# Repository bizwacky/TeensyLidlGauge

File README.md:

# Teensy Lidl Gauge

This is a set of gauges for my BMW E30 rally car, designed to be viewed in the peripheral vision, alerting to situations that need attention or immediate action and otherwise mostly being ignored while my OODA loop focuses on the stage ahead.

Three ER-TFT2.79-1 bar displays (NV3007 controller), driven over SPI by a
SparkFun MicroMod Teensy ,
fed by CAN data from the rusEFI ECU (a Super uaEFI), the JK BMS and the
car's two planned dingoFW PDMs. The gauge also reads the roof switch panel (six
switches, five pots) and sends it to the PDMs over CAN - it is the car's
light-switch node - and drives three PWM speed signals for the cabin fans.

This repository holds the firmware (`src/`, `lib/`, `docs/`) and, in
[`hardware/`](hardware/), the KiCad project, fab outputs and the 3D-printed
enclosure. The full hardware/software plan (`Rally CAN Gauge Project Plan`)
lives outside this repository.

**Status (Nov 2026):** the v1.0 board is at the ordering stage.

## Design philosophy

- Most of the time the right amount of attention to pay the gauge is none. 
-  Red: The car is about to blow up.
  Yellow: Start worrying, keep an eye on it. Blue: information. A one-line
  banner names the problem (`OIL LOW`, `PUMP FLT`), critical banners flash
  at 1 Hz, and  have GPWS-style voice callouts
- Input code establishes what is (temperatures, pressures, link freshness); one alarm table decides what
  matters; the screens, LEDs and audio only render its verdicts. No
  display code ever touches a threshold. 
- A dead sensor or a dropped CAN link draws as
  `--`. Stale data raises no alarms of its own.
- The rotary dial is the only control: bright,
- medium, dark (night colours turn every blue element amber, which is kinder
  to dark-adapted eyes), debug, silent, fuel fill and displays off. One more
  detent, well away from those, is a car-park light show.
- All vehicle I/O comes through one sealed 26-pin Superseal. The 12 V front end has reverse-polarity protection, a
  36 V TVS, a switching 5 V module and a separate 3.3 V LDO. The fuel
  record (in CRC'd rotating slots) and a black-box log live in F-RAM, a hardware watchdog resets hung
  firmware within a second. 

## Hardware

100 x 100 mm, four layers (Signal / GND / GND / Signal), 1.6 mm, laid out in
KiCad 10 against JLCPCB's rules and their JLC04161H-7628 stackup. The J2 pin-out is printed on the back of the board.

| Block | Parts |
|---|---|
| Processor | SparkFun MicroMod Teensy in a TE 2199230-4 M.2 (E-key) socket |
| Displays | 3x ER-TFT2.79-1 on 10-pin 0.5 mm FPC connectors (Amphenol SFV10R-2STE1HLF), one SPI bus each; PWM backlights through three low-side N-FETs |
| Vehicle connector | TE Superseal 1.0, 26-pin (6473711-1): +12 V, CAN, six switch inputs, five pots, fuel sender, rotary dial, speaker, LED-strip data and 5 V, three fan PWM outputs |
| CAN | TI TCAN1051HGV-Q1 |
| Power | Traco TSR 3-2450N (5 V, 3 A), TI TLV75733P (3.3 V LDO), Panjit PJQ4465AP reverse-polarity P-FET, SMCJ36CA TVS |
| Logging and sensors | 1 Mbit I2C F-RAM (FM24VN10 / FM24V10), ST LSM6DSV320X IMU (±320 g), CR2450 cell for the clock |
| Audio | DFRobot DFPlayer Mini (DFR0299)|
| USB | 6-pin JST-PH (J1) to an Adafruit 6153 panel-mount USB-C, TPD2E2U06 ESD protection |

### What is in `hardware/`

| Path | What |
|---|---|
| `TeensyLidlGauge.kicad_pro`, `.kicad_pcb`, `.kicad_dru` and eight `.kicad_sch` sheets | KiCad 10 project: schematic, routed board, custom design rules |
| `Library.pretty/`, `Parts/`, `3dmodels/` | the footprints, symbols and 3D models made for this project, at the project-relative paths the design expects (third-party library files are left out; see below) |
| `Gerb/` | Gerbers and drill files, plus `TeensyLidlGauge-Gerb.zip` ready to upload |
| `BOM/` | `JLCPCB_BOM_upload.csv` (LCSC part numbers) and `Pikkolo_BOM_upload.csv` (MPNs and distributor part numbers) |
| `place/` | pick-and-place: `TeensyLidlGauge-JLC-CPL.csv` (JLCPCB format) and `TeensyLidlGauge-all-pos.csv` (KiCad format) |
| `Enclosure/` | printable STLs, a STEP fit-check assembly, renders |
| `renders/` | the PCB renders above |

Ordering notes:

- Left off both BOMs on purpose: J3 to J5 (9-pin display breakout headers,
  do not populate) and H2 to H5 (M3 mounting holes).

### Third-party library files

Some symbols, footprints and 3D models came from SnapEDA, Ultra Librarian,
LCSC/EasyEDA or the part makers, whose terms allow sharing a board design
built with them but not re-uploading the library files themselves. Those
files are not in this repository. Every footprint and symbol is still
embedded in the `.kicad_pcb` and the schematic, so the project opens,
checks and plots without them. KiCad may warn that the library copies are
missing, and the 3D viewer shows these parts without bodies. For the full
3D view, download the models by part number and save them at the paths
given in each footprint's 3D model settings (most are under `Parts/`).

| Ref | Part | Not included |
|---|---|---|
| U1 | TI TCAN1051HGVDRBRQ1 | footprint, symbol, 3D model |
| U2 | TI TLV75733PDRVR | footprint, symbol, 3D model |
| U3 | ST LSM6DSV320XTR | symbol |
| U4 | TE 2199230-4 (M.2 socket) | 3D model |
| U5 | TI TPD2E2U06QDBZRQ1 | footprint, symbol, 3D model |
| U7 | DFRobot DFR0299 | footprint, symbol, 3D model |
| Q2 | Panjit PJQ4465AP-AU_R2_000A1 | footprint, symbol |
| D1 | onsemi SZBZX84C16LT1G | footprint, symbol, 3D model |
| CR1 | Littelfuse SMCJ36CA | symbol |
| PS1 | Traco TSR 3-2450N | footprint, symbol, 3D model |
| S1 | Würth 435171014816 | footprint, symbol, 3D model |
| BT1 | MYOUNG BS-24-B4AK014 | footprint, symbol, 3D model |
| J1 | JST B6B-PH-SM4-TB | symbol |
| J2 | TE 6473711-1 (Superseal) | footprint, 3D model |
| J6 to J8 | Amphenol SFV10R-2STE1HLF | footprint, symbol, 3D model |

### Enclosure

*Shrimplify, and add lightness.*

| File | What |
|---|---|
| `tray_R2_b2.stl` | tray: holds the PCB and the display bar |
| `cover_R2_bloom.stl` | patterned cover |
| `clamp_saddle_1p75in.stl`, `clamp_cap_1p75in.stl` | dash-bar clamp halves for a 1.75 in tube (the renders use two clamps) |
| `assembly_R2_reference.step` | fit-check assembly with the PCB, lens and mask, USB-C, clamps and a 1.75 in bar (it uses unpatterned versions of the tray and cover) |

## Firmware layout

- `src/main.cpp` - the superloop (scheduler + 1 Hz debug print).
- `src/config.h` - every pin, constant, threshold and tunable in one place.
- `src/vehicle_data.h/.cpp` - the central data model (`g_data`), including
  the alarm catalog enum (ordered by the plan's priorities).
- `src/alarms.h/.cpp` - the warning/alarm state machine: one table row per
  alarm (name, color, tier, persistence, audio clip, condition), 36 rows in
  priority order. The PDM rows class a fault by what it costs (engine,
  cooling, vision, body) and name the load on the banner (`PUMP FLT`).
- `src/led_tach.h/.cpp` - the WS2812 strip: 3 status LEDs, the 12-LED tach
  and shift light, plus the switch-label backlights wired onto the end of
  the same chain (one steady color, never part of the flashing).
- `src/audio.h/.cpp` - voice-callout arbitration (priority, repeat intervals,
  no talking over itself) plus the DFPlayer Mini driver (Makuna/DFMiniMp3 on
  Serial7, pins 28/29, watchdog-safe NoAck mode - design notes at the top
  of the .cpp).
  SD card layout is documented on the clip enum in `audio.h`; the rotary
  dial's silent position (`MODE_SILENT`) mutes all callouts.
- `src/backlight.h/.cpp` - display backlight dimming: 20 kHz PWM into three
  low-side N-FET switches (pins 9/33/4 - all on FlexPWM2 so the three
  windows can be locked a third of a period apart: the 5V rail sees one
  100 mA step at a time instead of 300 mA), brightness from the rotary mode
  with per-screen binning trim (`BL_TRIM`) and a 250 ms fade between
  levels. Hardware, frequency and phase rationale in `config.h`; the
  FlexPWM register mechanics and the bench check at the top of the .cpp.
- `src/lightshow.h/.cpp` - the light show on dial position 9 (prototype,
  never run on hardware): a music track from the DFPlayer with the LED
  strip, screens, backlights and - through one more CAN frame to the PDMs -
  the exterior lamps flashing in time. This file is the state machine: the
  dial gesture, the countdown, the interlocks (it only starts when the dial
  arrives there, and a red alarm or an engine above idle ends it) and the
  open-loop clock that follows the music.
- `src/lightshow_fx.h/.cpp` - what the lights do at each moment: a pure
  function from position-in-the-track to one frame, driven by a one-line
  "map" per track in `config.h`. It is compiled unchanged into the browser
  simulator and the host tests under `tools/lightshow/`.
  **See `docs/LIGHTSHOW.md`** for use, calibration, adding a track and limits.
- `src/watchdog.h/.cpp` - minimal register driver for the i.MX RT's WDOG1.
- `src/can_bus.h/.cpp` - CAN3 + the decoders: rusEFI's native broadcast
  (frames BASE0..7, layouts from rusEFI's own DBC), the one target-AFR byte
  from rusEFI's MS Simplified broadcast, the JK BMS Deye protocol (1 Hz)
  and both PDMs' dingoFW status frames (10 Hz, driven by the `PDM_FRAMES`
  table in `config.h`) - all little-endian. It transmits the 1 Hz PCS
  heartbeat the BMS expects from an "inverter" and the two frames that
  carry the roof switches and pots to the PDMs (10 Hz + on change; every
  switch is sent as an on bit and an off bit so the PDM config can make
  lamps fail ON). Every frame is counted as decoded, ignored (expected
  traffic we don't use) or unknown, so a misconfigured bus shows up as
  `unk=`.
- `src/pdm.h/.cpp` - what the PDM status means: a verdict per output (OK /
  TRP tripped / OPN open load / FLT faulted or stuck) with the memory those
  need, the lamp states the indicator icons and night mode read, and the
  last output event for the black box. Rules and the dingoFW behaviour they
  rest on at the top of the .cpp.
- `src/fans.h/.cpp` - three 25 kHz PWM speed signals for the defrost and
  seat fans, each set by a roof-panel pot.
- `src/mixture.h/.cpp` - the gated two-second lambda window the AFR alarms
  judge: samples only count while the driver is on the throttle, rusEFI
  isn't cutting fuel, and the sensor has recovered from the last time that
  wasn't true - so overrun and fuel cut can't raise AFR LEAN.
- `src/inputs.h/.cpp` - fuel sender (ratiometric 150R divider, including
  the two-stage slosh filter: median window + slow EMA), rotary switch
  (4.7k pull-up into eleven resistors chosen for even voltage steps, decoded
  by nearest expected ratio, with open-wiper detection feeding the DIALFAIL
  alarm and a fail-safe fallback to Bright), the roof panel's six
  ground-switched switches (debounced) and five pots (rheostats, percent of
  travel, open-wire failsafe), chip temp, RTC. The circuits are drawn in
  `config.h`.
- `src/fuel_calc.h/.cpp` - calculated fuel: integrates the ECU's injector
  pulse width (dead-time corrected) into a gallons-remaining estimate, and
  runs the rotary FUEL FILL gesture (hold 30 s = +5 gal, 60 s = full tank).
  Physics and design rationale at the top of the .cpp; constants in
  `config.h`. Seeds from the FRAM fuel record at boot (sender fallback).
- `src/fram.h/.cpp` - FM24V10 F-RAM driver: non-blocking I2C write queue
  (interrupt-driven via teensy4_i2c - the superloop never waits on the
  bus), blocking reads for boot/console, shared CRC-16.
- `src/fram_log.h/.cpp` - what the FRAM stores: the persistent fuel record
  (16 rotating CRC'd slots - kill-switch-proof) and the black-box flight
  recorder (~1.8 h circular log of every gauge field, PDM temperatures and
  output events, roof switches + active alarms), plus
  the serial console (`h` in the monitor: CSV dump, fuel slots, format).
  **See `docs/FRAM_BLACKBOX.md`** for the memory map, record formats,
  wiring, and how to read the log out.
- `src/gauge_render.h/.cpp` - what the three panels show: the bench-tested
  prototype layouts (big value left, secondary stack right), the semantic
  color Theme (night mode = every blue element turns amber, resolved in one
  place), per-readout coloring from alarm verdicts, the warning banner with
  its 1 Hz critical flash, and the MODE_DEBUG dense pages. Stateless: every
  frame is composed from scratch from g_data ("compose then show", like the
  LED strip). Design story at the top of the .cpp.
- `src/screens.h/.cpp` - how frames reach the glass: three ILI9341_T4
  drivers (one per SPI bus), one shared 121 KB draw buffer + three
  per-display internal buffers in OCRAM, differential DMA updates, the
  busy-skip rule that keeps the superloop from ever blocking on a transfer,
  and displays-off handling. Memory map + pipeline at the top of the .cpp.
- `src/fonts/` - the custom Iosevka faces (tgx font exports, PROGMEM):
  Regular 30 px for labels, Heavy 30 px for the banner, Extended 55/114 px
  for values. Monospaced so a changing digit dirties only its own cell
  (small diffs). Regenerate with vindar's tgx font tool from the Iosevka
  TTFs; the PC prototype (the local `Graphics/` folder, not in this
  repository) is the layout source of truth.
- `src/examples/display_bringup.cpp` - display test pattern, built by the
  `display_test` environment (wiring documented at the top of the file).
- `docs/FRAM_BLACKBOX.md` - the FM24V10 wiring, memory map, record
  formats, black-box gating rules, and the serial console commands.
- `docs/ECU_CAN_SETUP.md` - **the rusEFI / TunerStudio settings the firmware
  expects** (broadcast base address, dash type, period), the frame map, and
  the bring-up checklist. Keep it in sync with `config.h`/`can_bus.cpp`.
- `docs/BMS_CAN_SETUP.md` - the JK BMS protocol selection (Deye/001), the
  frames decoded, BMS bring-up checks, and the table of every CAN id on the
  bus.
- `docs/PDM_CAN_SETUP.md` - **the dingoConfig settings the firmware
  expects**: Base IDs, the status frames decoded (including the proposed
  frames for outputs 9-14), the two frames the gauge sends, the CAN-input
  recipe that makes lamps fail on, and the bench checks.
- `docs/LIGHTSHOW.md` - the light show: how to use and calibrate it, the
  SD card layout, how to add a track, and what limits each light source.
- `tools/lightshow/` - the light show's host tests, its browser simulator
  (`lightshow_sim.html`, built from the firmware source by `build.sh`) and
  the calibration click-track generator. Nothing here is flashed.
- `lib/ILI9341_T4/` - vindar's ILI9341_T4 DMA display library, modified for
  the NV3007 controller. **Read `lib/ILI9341_T4/PORTING_NV3007.md`** for a
  walkthrough of every change and why it was needed. It is vendored from
  upstream v1.7.1 (commit `bee2957`, https://github.com/vindar/ILI9341_T4);
  diff against that commit to see the exact modifications.

## Display driving in one paragraph

Each display gets its own SPI bus (display 1 on SPI2, display 2 on SPI1,
display 3 on SPI). We draw into a
428x142 RGB565 framebuffer in RAM, then `tft.update(fb)` hands it to the
library, which diffs it against what is already on screen and streams only
the changed pixels out via DMA - the CPU is free almost the entire time.
VSync is not available (the display has no MISO line to poll the scanline),
but the TE pin is broken out on the module and reserved in the pinout for a
possible future tear-free sync mod.

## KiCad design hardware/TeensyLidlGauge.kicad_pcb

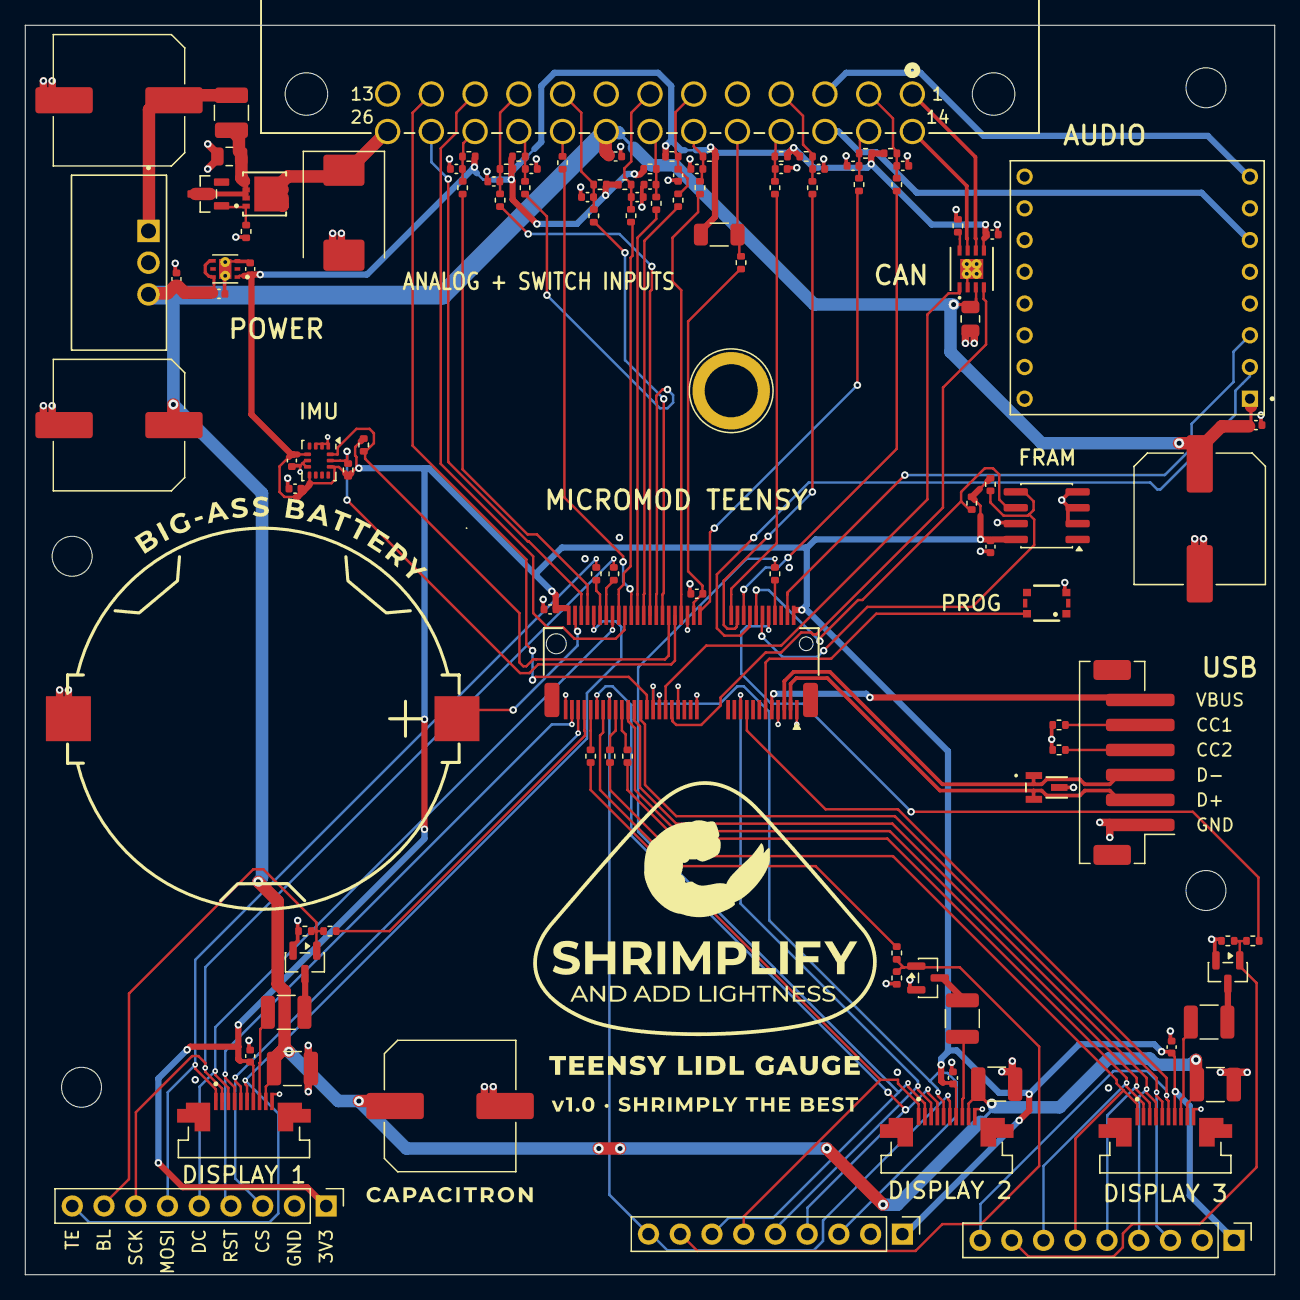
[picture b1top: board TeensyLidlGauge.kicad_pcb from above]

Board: 4 copper layers, 100.0 x 100.0 mm, 115 parts (0 on the bottom side), 94 nets.

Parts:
BT1: BS-24-B4AK014; BAT-SMD_BS-24-B4AK014
C2, C3, C12, C14, C15, C20, C21, C22, C24, C25, C26, C27, C28, C29, C30, C31, C32, C33, C34, C35, C36: 100nF; C_0402_1005Metric
C4, C11, C13: 22 μF; C_1210_3225Metric
C5, C10: 4.7 μF; C_0805_2012Metric
C6, C8, C9, C16, C17: 1 μF; C_0402_1005Metric
C7, C23, C37, C38: 100 μF; C_Elec_10x10.2
CR1: SMCJ36CA; D_SMC
D1: SZBZX84C16LT1G; SOT95P240X111-3N
H1: MicroMod_Standoff; MicroMod_Standoff_M2.5_SMTSO2525
H2, H3, H4, H5: MountingHole; MountingHole_3.2mm_M3_ISO14580
J1: B6B-PH-SM4-TB; JST_PH_B6B-PH-SM4-TB_1x06-1MP_P2.00mm_Vertical
J2: 6473711-1; CON26_2X13_SUPERSEAL_TYC
J3: Display1 breakout; PinHeader_1x09_P2.54mm_Vertical_DisplayBreakout
J4: Display2 breakout; PinHeader_1x09_P2.54mm_Vertical_DisplayBreakout
J5: Display3 breakout; PinHeader_1x09_P2.54mm_Vertical_DisplayBreakout
J6, J7, J8: SFV10R-2STE1HLF; AMPHENOL_SFV10R-2STE1HLF
L1: 10 μH; L_1210_3225Metric
PS1: TSR_3-2450N; CONV_TSR_3-2450N
Q1, Q6, Q7: AO3400A; SOT-23
Q2: PJQ4465AP-AU_R2_000A1; DFN3333-8L_PNJ
R1, R3, R32, R35: 470 ohm; R_0402_1005Metric
R2, R33, R36: 100 kohm; R_0402_1005Metric
R8, R34, R37: 21 ohm; R_1210_3225Metric
R11: 10 kohm; R_0402_1005Metric
R13, R15, R22, R23, R26, R27: 2.2 kohm; R_0402_1005Metric
R14: 150 ohm; R_1206_3216Metric
R16, R17, R18, R19, R20, R21: 33 ohm; R_0402_1005Metric
R24, R25: 5.1 kohm; R_0402_1005Metric
R44, R46, R48, R50, R52, R54, R56, R58, R60, R62, R64, R67: 22 kohm; R_0402_1005Metric
R45, R47, R49, R51, R53, R55, R57, R59, R61, R63, R65, R66: 4.7 kohm; R_0402_1005Metric
S1: 435171014816
U1: TCAN1051HGVDRBRQ1; DRB8_TEX
U2: TLV75733PDRVR; VREG_TLV75733PDRVR
U3: LSM6DSV320XTR; LGA-14_3x2.5mm_P0.5mm_ST_LSM6DSV
U4: Teensy4.0; MicroMod_M.2-E_TE_2199230-4
U5: TPD2E2U06QDBZRQ1; DBZ0003A_TEX
U7: DFR0299; MODULE_DFR0299
U8: FM24VN10-G; SOIC-8_3.9x4.9mm_P1.27mm

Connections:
+3V3: C2.2, C8.2, C14.1, C17.2, C20.2, C21.1, C22.1, C35.2, C36.2, J3.1, J4.1, J5.1, J6.7 (+3.3V), J7.7 (+3.3V), J8.7 (+3.3V), R14.1, R15.1, R22.1, R26.1, R27.1, R45.1, R47.1, R49.1, R51.1, R53.1, R55.1, R57.1, R59.1, R61.1, R63.1, R65.1, R66.1, U1.5 (Vio), U2.1 (OUT), U3.5 (VDDIO), U3.8 (VDD), U3.12 (CS), U4.2 (3V3_IN), U4.74 (3V3_IN), U8.8 (VDD)
+5V: C3.1, C4.1, C5.2, C6.1, C7.1, C9.2, C11.1, C13.1, C16.2, C37.1, C38.1, J2.21 (+5V), J6.9 (LEDA), J7.9 (LEDA), J8.9 (LEDA), PS1.3 (+VOUT), U1.3 (VCC), U2.4 (EN), U2.6 (IN), U7.1 (VCC)
+12V: CR1.1, J2.26 (+12V), Q2.5, Q2.6, Q2.7, Q2.8
/Teensy/BAT_PWR: BT1.1, U4.72 (VBAT)
/Teensy/FRAM_SCL: R22.2, U4.14 (19_FRAM_SCL), U8.6 (SCL)
/Teensy/FRAM_SDA: R15.2, U4.12 (18_FRAM_SDA), U8.5 (SDA)
CANH: J2.14 (CAN_H), U1.7 (CANH)
CANL: J2.1 (CANL), U1.6 (CANL)
CAN_RX: U1.4 (RXD), U4.41 (30_CAN_RX)
CAN_TX: U1.1 (TXD), U4.43 (31_CAN_TX)
DIAL_IN: C15.1, J2.19 (DIAL), R66.2, R67.1
DIAL_READ: R67.2, U4.38 (15_Switch_Rotary)
Display1BL: J3.8, Q1.1 (G), R2.1, R3.1
Display1CS: J3.3, J6.5 (CS), U4.71 (6_Display1_CS)
Display1DC: J3.5, J6.3 (DC), U4.60 (36_SPI2_DC)
Display1MOSI: J3.6, J6.1 (MOSI), R21.2
Display1PWM: R3.2, U4.69 (9_Display1_PWM)
Display1RST: J3.4, J6.4 (RST), U4.73 (45_Display1_RESET)
Display1SCK: J3.7, J6.2 (SCK), R20.2
Display1TE: J3.9, J6.6 (TE), U4.66 (34_Display1_TE)
Display2BL: J4.8, Q6.1 (G), R32.1, R33.1
Display2CS: J4.3, J7.5 (CS), U4.47 (2_Display2_CS)
Display2DC: J4.5, J7.3 (DC), U4.19 (0_SPI1_DC)
Display2MOSI: J4.6, J7.1 (MOSI), R18.2
Display2PWM: R32.2, U4.63 (33_Display2_PWM)
Display2RST: J4.4, J7.4 (RST), U4.65 (32_Display2_RESET)
Display2SCK: J4.7, J7.2 (SCK), R19.2
Display2TE: J4.9, J7.6 (TE), U4.61 (12_Display2_TE)
Display3BL: J5.8, Q7.1 (G), R35.1, R36.1
Display3CS: J5.3, J8.5 (CS), U4.51 (25_Display3_CS)
Display3DC: J5.5, J8.3 (DC), U4.55 (10_SPI0_DC)
Display3MOSI: J5.6, J8.1 (MOSI), R17.1
Display3PWM: R35.2, U4.10 (4_Display3_PWM)
Display3RST: J5.4, J8.4 (RST), U4.53 (24_Display3_RESET)
Display3SCK: J5.7, J8.2 (SCK), R16.1
Display3TE: J5.9, J8.6 (TE), U4.17 (1_Display3_TE)
FUEL_IN: J2.18 (FUEL), R13.1, R14.2
FUEL_READ: C12.1, R13.2, U4.34 (14_FUEL_SENDER)
GND: BT1.2, C2.1, C3.2, C4.2, C5.1, C6.2, C7.2, C8.1, C9.1, C10.1, C11.2, C12.2, C13.2, C14.2, C15.2, C16.1, C17.1, C20.1, C21.2, C22.2, C23.2, C24.2, C25.2, C26.2, C27.2, C28.2, C29.2, C30.2, C31.2, C32.2, C33.2, C34.2, C35.1, C36.1, C37.2, C38.2, CR1.2, H1.1 (1_1), J1.1 (GND), J2.5 (GND), J2.8 (GND), J2.13 (GND), J3.2, J4.2, J5.2, J6.10 (GND), J7.10 (GND), J8.10 (GND), PS1.2 (GND), Q1.2 (S), Q6.2 (S), Q7.2 (S), R2.2, R11.1, R23.1, R24.1, R25.1, R33.2, R36.2, S1.3, U1.2 (GND), U1.9 (EPAD), U2.3 (GND), U2.7 (EXP), U3.1 (SDO/TA0), U3.2 (SDX), U3.3 (SCX), U3.6 (GND), U3.7 (GND), U4.1 (GND), U4.7 (GND), U4.33 (GND), U4.36 (GND), U4.39 (GND), U4.45 (GND), U4.75 (GND), U5.3 (GND), U7.7 (GND), U7.10 (GND__1), U8.2 (A1), U8.3 (A2), U8.4 (VSS), U8.7 (WP)
IMU_SCL: R26.2, U3.13 (SCL), U4.40 (40_IMU_SCL)
IMU_SDA: R27.2, U3.14 (SDA), U4.42 (41_IMU_SDA)
LED_DATA: R1.2, U4.54 (8_LED_Serial)
MP3_RX: U4.4 (28_MP3_RX), U7.3 (TX)
MP3_TX: U4.16 (29_MP3_TX), U7.2 (RX)
unnamed: C10.2, D1.3, L1.1, Q2.1, Q2.2, Q2.3
unnamed: D1.1, Q2.4, R11.2
unnamed: J1.5 (CC1), R25.2
unnamed: J1.4 (CC2), R24.2
unnamed: J2.22 (LED), R1.1
unnamed: J6.8 (LEDK), R8.2
unnamed: J7.8 (LEDK), R34.2
unnamed: J8.8 (LEDK), R37.2
unnamed: C23.1, L1.2, PS1.1 (+VIN)
unnamed: Q1.3 (D), R8.1
unnamed: Q6.3 (D), R34.1
unnamed: Q7.3 (D), R37.1
unnamed: R23.2, U1.8 (S)
unnamed: R17.2, U4.59 (11_SPI0_MOSI)
unnamed: R16.2, U4.57 (13_SPI0_SCK)
unnamed: R18.1, U4.67 (26_SPI1_MOSI)
unnamed: R19.1, U4.8 (27_SPI1_SCK)
unnamed: R21.1, U4.64 (35_SPI2_MOSI)
unnamed: R20.1, U4.62 (37_SPI2_SCK)
unnamed: S1.2, U4.11 (PROGRAM)
PWM_1: J2.11 (PWM1), U4.56 (7_PWM_1)
PWM_2: J2.12 (PWM2), U4.49 (22_PWM_2)
PWM_3: J2.25 (PWM3), U4.70 (39_PWM_3)
Pot_1_IN: C30.1, J2.6 (POT1), R56.1, R57.2
Pot_1_READ: R56.2, U4.50 (21_Pot_1)
Pot_2_IN: C31.1, J2.7 (POT2), R58.1, R59.2
Pot_2_READ: R58.2, U4.58 (23_Pot_2)
Pot_3_IN: C32.1, J2.20 (POT3), R60.1, R61.2
Pot_3_READ: R60.2, U4.52 (20_Pot_3)
Pot_4_IN: C33.1, J2.4 (POT4), R62.1, R63.2
Pot_4_READ: R62.2, U4.20 (16_Pot_4)
Pot_5_IN: C34.1, J2.17 (POT5), R64.1, R65.2
Pot_5_READ: R64.2, U4.22 (17_Pot_5)
SPK+: J2.16 (SPK+), U7.6 (SPK1)
SPK-: J2.3 (SPK-), U7.8 (SPK2)
Switch_1_IN: C24.1, J2.2 (SW1), R44.1, R45.2
Switch_1_READ: R44.2, U4.18 (5_Switch_1)
Switch_2_IN: C25.1, J2.15 (SW2), R46.1, R47.2
Switch_2_READ: R46.2, U4.32 (3_Switch_2)
Switch_3_IN: C26.1, J2.9 (SW3), R48.1, R49.2
Switch_3_READ: R48.2, U4.44 (42_Switch_3)
Switch_4_IN: C27.1, J2.23 (SW4), R50.1, R51.2
Switch_4_READ: R50.2, U4.46 (43_Switch_4)
Switch_5_IN: C28.1, J2.10 (SW5), R52.1, R53.2
Switch_5_READ: R52.2, U4.48 (44_Switch_5)
Switch_6_IN: C29.1, J2.24 (SW6), R54.1, R55.2
Switch_6_READ: R54.2, U4.68 (38_Switch_6)
USB D+: J1.2 (D+), U4.3 (USB_D+), U5.2 (IO2)
USB D-: J1.3 (D-), U4.5 (USB_D-), U5.1 (IO1)
VUSB: J1.6 (VUSB), U4.9 (USB_VIN)

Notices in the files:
parts and their libraries:
Pad geometry from SparkFun's production MicroMod connector footprint (CC BY 4.0).
